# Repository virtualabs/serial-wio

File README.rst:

Serial-Wio
==========

Turn your WioTerminal into an automagic UART terminal !

Features
--------

* Automatic baudrate/parity detection
* On-screen UART log
* USB UART bridge

Case printing and assembly
--------------------------

A custom case has been designed to fit the WioTerminal, it allows normal multimeter probes
to be used and protects the electronics.

The case is made of 3 independent parts that may be 3d printed with any decent 3d printer:

* a bottom part that holds 6 M3 hex screws
* a middle part that holds 2 M3 hex nuts
* a top part

Extra materials required:

* 2x 10mm M3 screws
* 4x 15mm M3 screws
* 2x M3 nuts

Printing the case
~~~~~~~~~~~~~~~~~

Top part must be printed upside down to get best results, without supports. Bottom part must be
printed with supports to get the screws' heads holes correctly printed.

Assembling the case
~~~~~~~~~~~~~~~~~~~

First, insert 2x 10mm M3 screws in the bottom part as shown below:

.. image:: images/assemblage-step1.png
  :alt: Assembling bottom part

Then, place the custom PCB inside the bottom part:

.. image:: images/assemblage-step2.png
  :alt: Insert Serial-Wio assembled PCB

Place on top of this the intermediate lid and add two M3 nuts. Tighten them just enough to hold the lid
in place. 

.. image:: images/assemblage-step3.png
  :alt: Place and secure intermediate lid in place

Last, place the top lid and screw 4x 15mm M3 screws to maintain it in place, as shown below:

.. image:: images/assemblage-step4.png
  :alt: Fix the top lid

You can now connect your WioTerminal to your SerialWio module:

.. image:: images/assemblage-final.png
  :alt: Place and secure intermediate lid in place

Custom PCB
----------

We designed a custom PCB that extends WioTerminal capabilities designed with KiCAD v5.
Design files are available in `PCB_design_files` folder, including 3D models and custom
fingerprints.

Gerber files
~~~~~~~~~~~~

Gerber files are also provided in the `PCB_design_files/gerber` directory, as well as the
`kicad_pcb` file if you want to order it on OSHPark. 

Bill of materials
~~~~~~~~~~~~~~~~~

* Q1, Q2, Q3: SOT23 MMBF170 N-channel MOSFET 60V 225mW (Ref LCSC: C130879)
* R1, R2, R3: R0805 10 Kohm (Ref LCSC: C269742)
* TEST_SIG1: 4mm banana female plug red (Farnell: SWEB 8094 AU/RT)
* TEST_GND1: 4mm banana female plug black (Farnell: SWEB 8094 AU/SW)
* 3 contacts (1 row) 2.54mm right-angled header

Software dependencies
---------------------

First, you need to follow the `Get Started with Wio Terminal <https://wiki.seeedstudio.com/Wio-Terminal-Getting-Started/>`_
guide in order to setup your Arduino development environment.

This project has been designed with Arduino and requires some libraries to successfully compile:

* `TFT_eSPI` to drive the LCD screen of the WioTerminal
* `SAMD_TimerInterrupt` to handle SAMD21 timers

Make sure to add them before trying to compile the import the Arduino sketch and build it (use Arduino's
library manager).

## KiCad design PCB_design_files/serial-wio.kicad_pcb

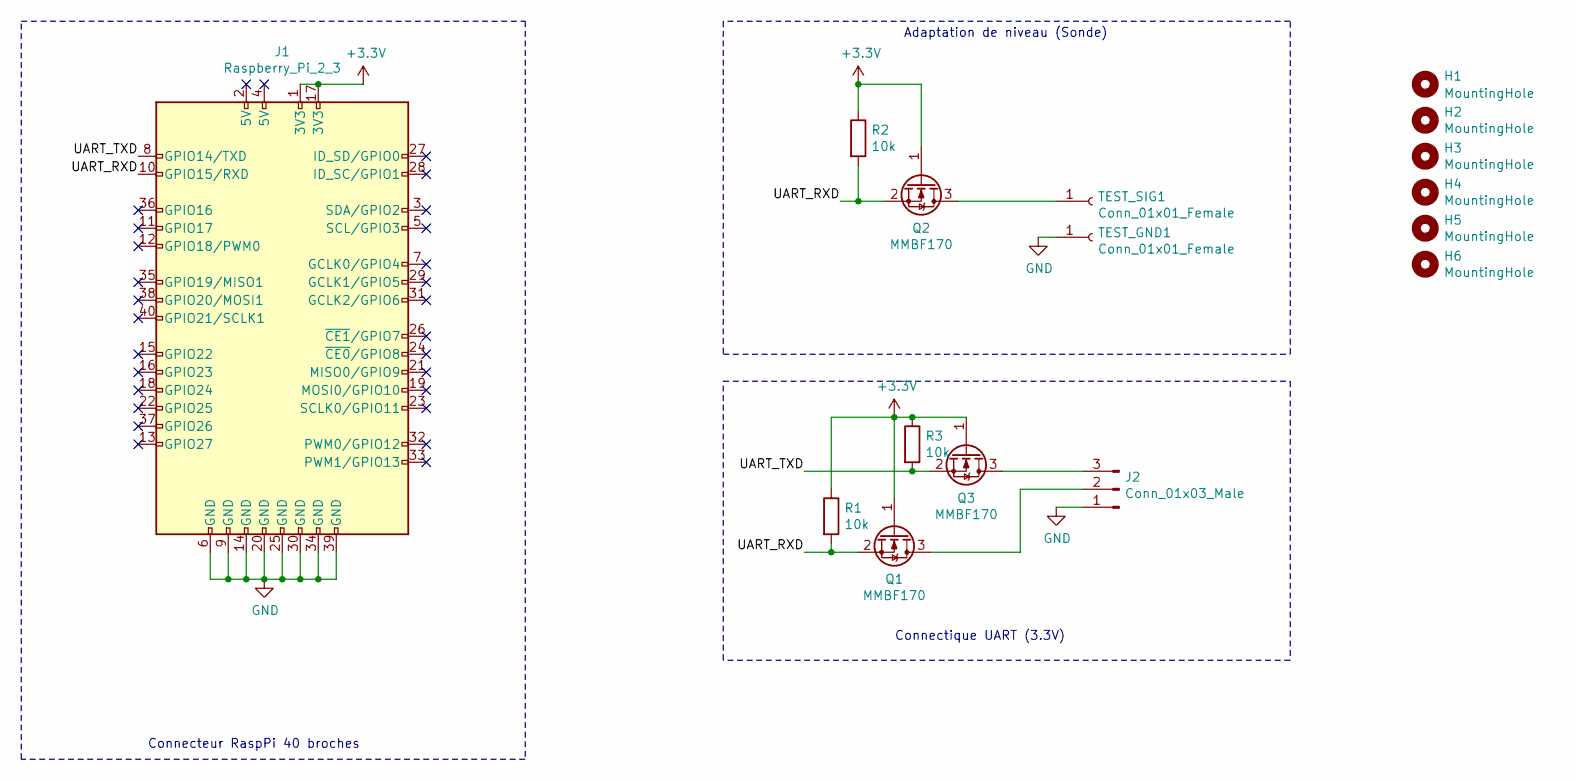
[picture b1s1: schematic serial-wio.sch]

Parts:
H1, H2, H3, H4, H5, H6: MountingHole; MountingHole_3.2mm_M3_Pad_Via
J1: Raspberry_Pi_2_3; PinHeader_2x20_P2.54mm_Vertical
J2: Conn_01x03_Male; PinHeader_1x03_P2.54mm_Horizontal
Q1, Q2, Q3: MMBF170; SOT-23
R1, R2, R3: 10k; R_0805_2012Metric
TEST_GND1: Conn_01x01_Female; 4mm-test-conn-socket
TEST_SIG1: Conn_01x01_Female; 4mm-test-conn-socket

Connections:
+3V3: J1.1 (3V3), J1.17 (3V3), Q1.1 (G), Q2.1 (G), Q3.1 (G), R1.1, R2.1, R3.1
/UART_RXD: J1.10 (GPIO15/RXD), Q1.2 (S), Q2.2 (S), R1.2, R2.2
/UART_TXD: J1.8 (GPIO14/TXD), Q3.2 (S), R3.2
GND: J1.6 (GND), J1.9 (GND), J1.14 (GND), J1.20 (GND), J1.25 (GND), J1.30 (GND), J1.34 (GND), J1.39 (GND), J2.1, TEST_GND1.1
unnamed: J2.2, Q1.3 (D)
unnamed: J2.3, Q3.3 (D)
unnamed: Q2.3 (D), TEST_SIG1.1

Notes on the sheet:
Connecteur RaspPi 40 broches
Adaptation de niveau (Sonde)
Connectique UART (3.3V)

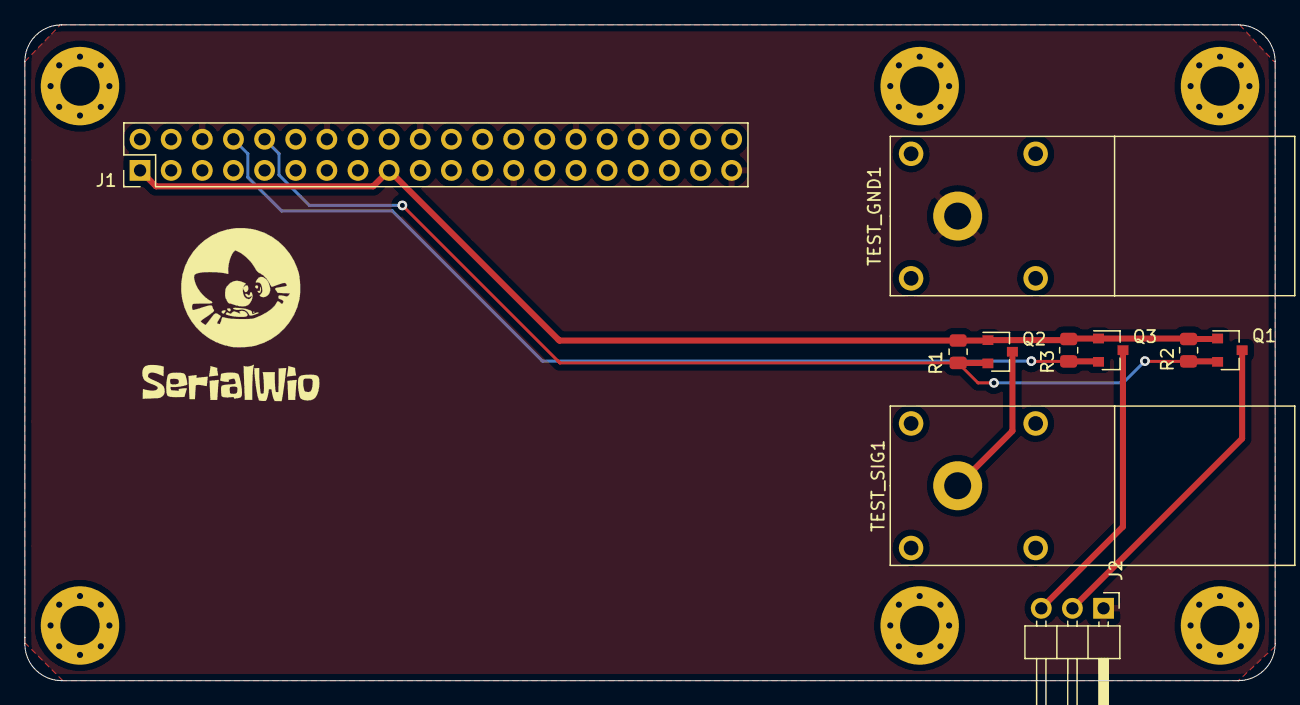
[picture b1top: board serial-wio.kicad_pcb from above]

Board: 2 copper layers, 102.0 x 53.5 mm, 17 parts (0 on the bottom side), 7 nets.

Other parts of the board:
kibuzzard-62313C45: G***; label

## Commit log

2022-03-09 First working PoC !
2022-03-09 Improved performances of try_decode()
2022-03-15 Improved UI + code cleaning
2022-03-15 Added README.rst
2022-03-15 Added buzzer sound when baudrate/parity found.
2022-03-16 Fixed a bug: clear screen was messy when in syncing mode.
2022-06-07 Added PCB and custom case design files.
2022-08-07 Added STL files and updated arduino code.
2022-08-07 Added building instructions.
2022-08-07 Images path fixed.
2022-08-07 Added BOM
2022-08-07 Pushed missing image.
2022-08-07 Added software building guide and dependencies.
2022-08-07 Fixed some typos.
